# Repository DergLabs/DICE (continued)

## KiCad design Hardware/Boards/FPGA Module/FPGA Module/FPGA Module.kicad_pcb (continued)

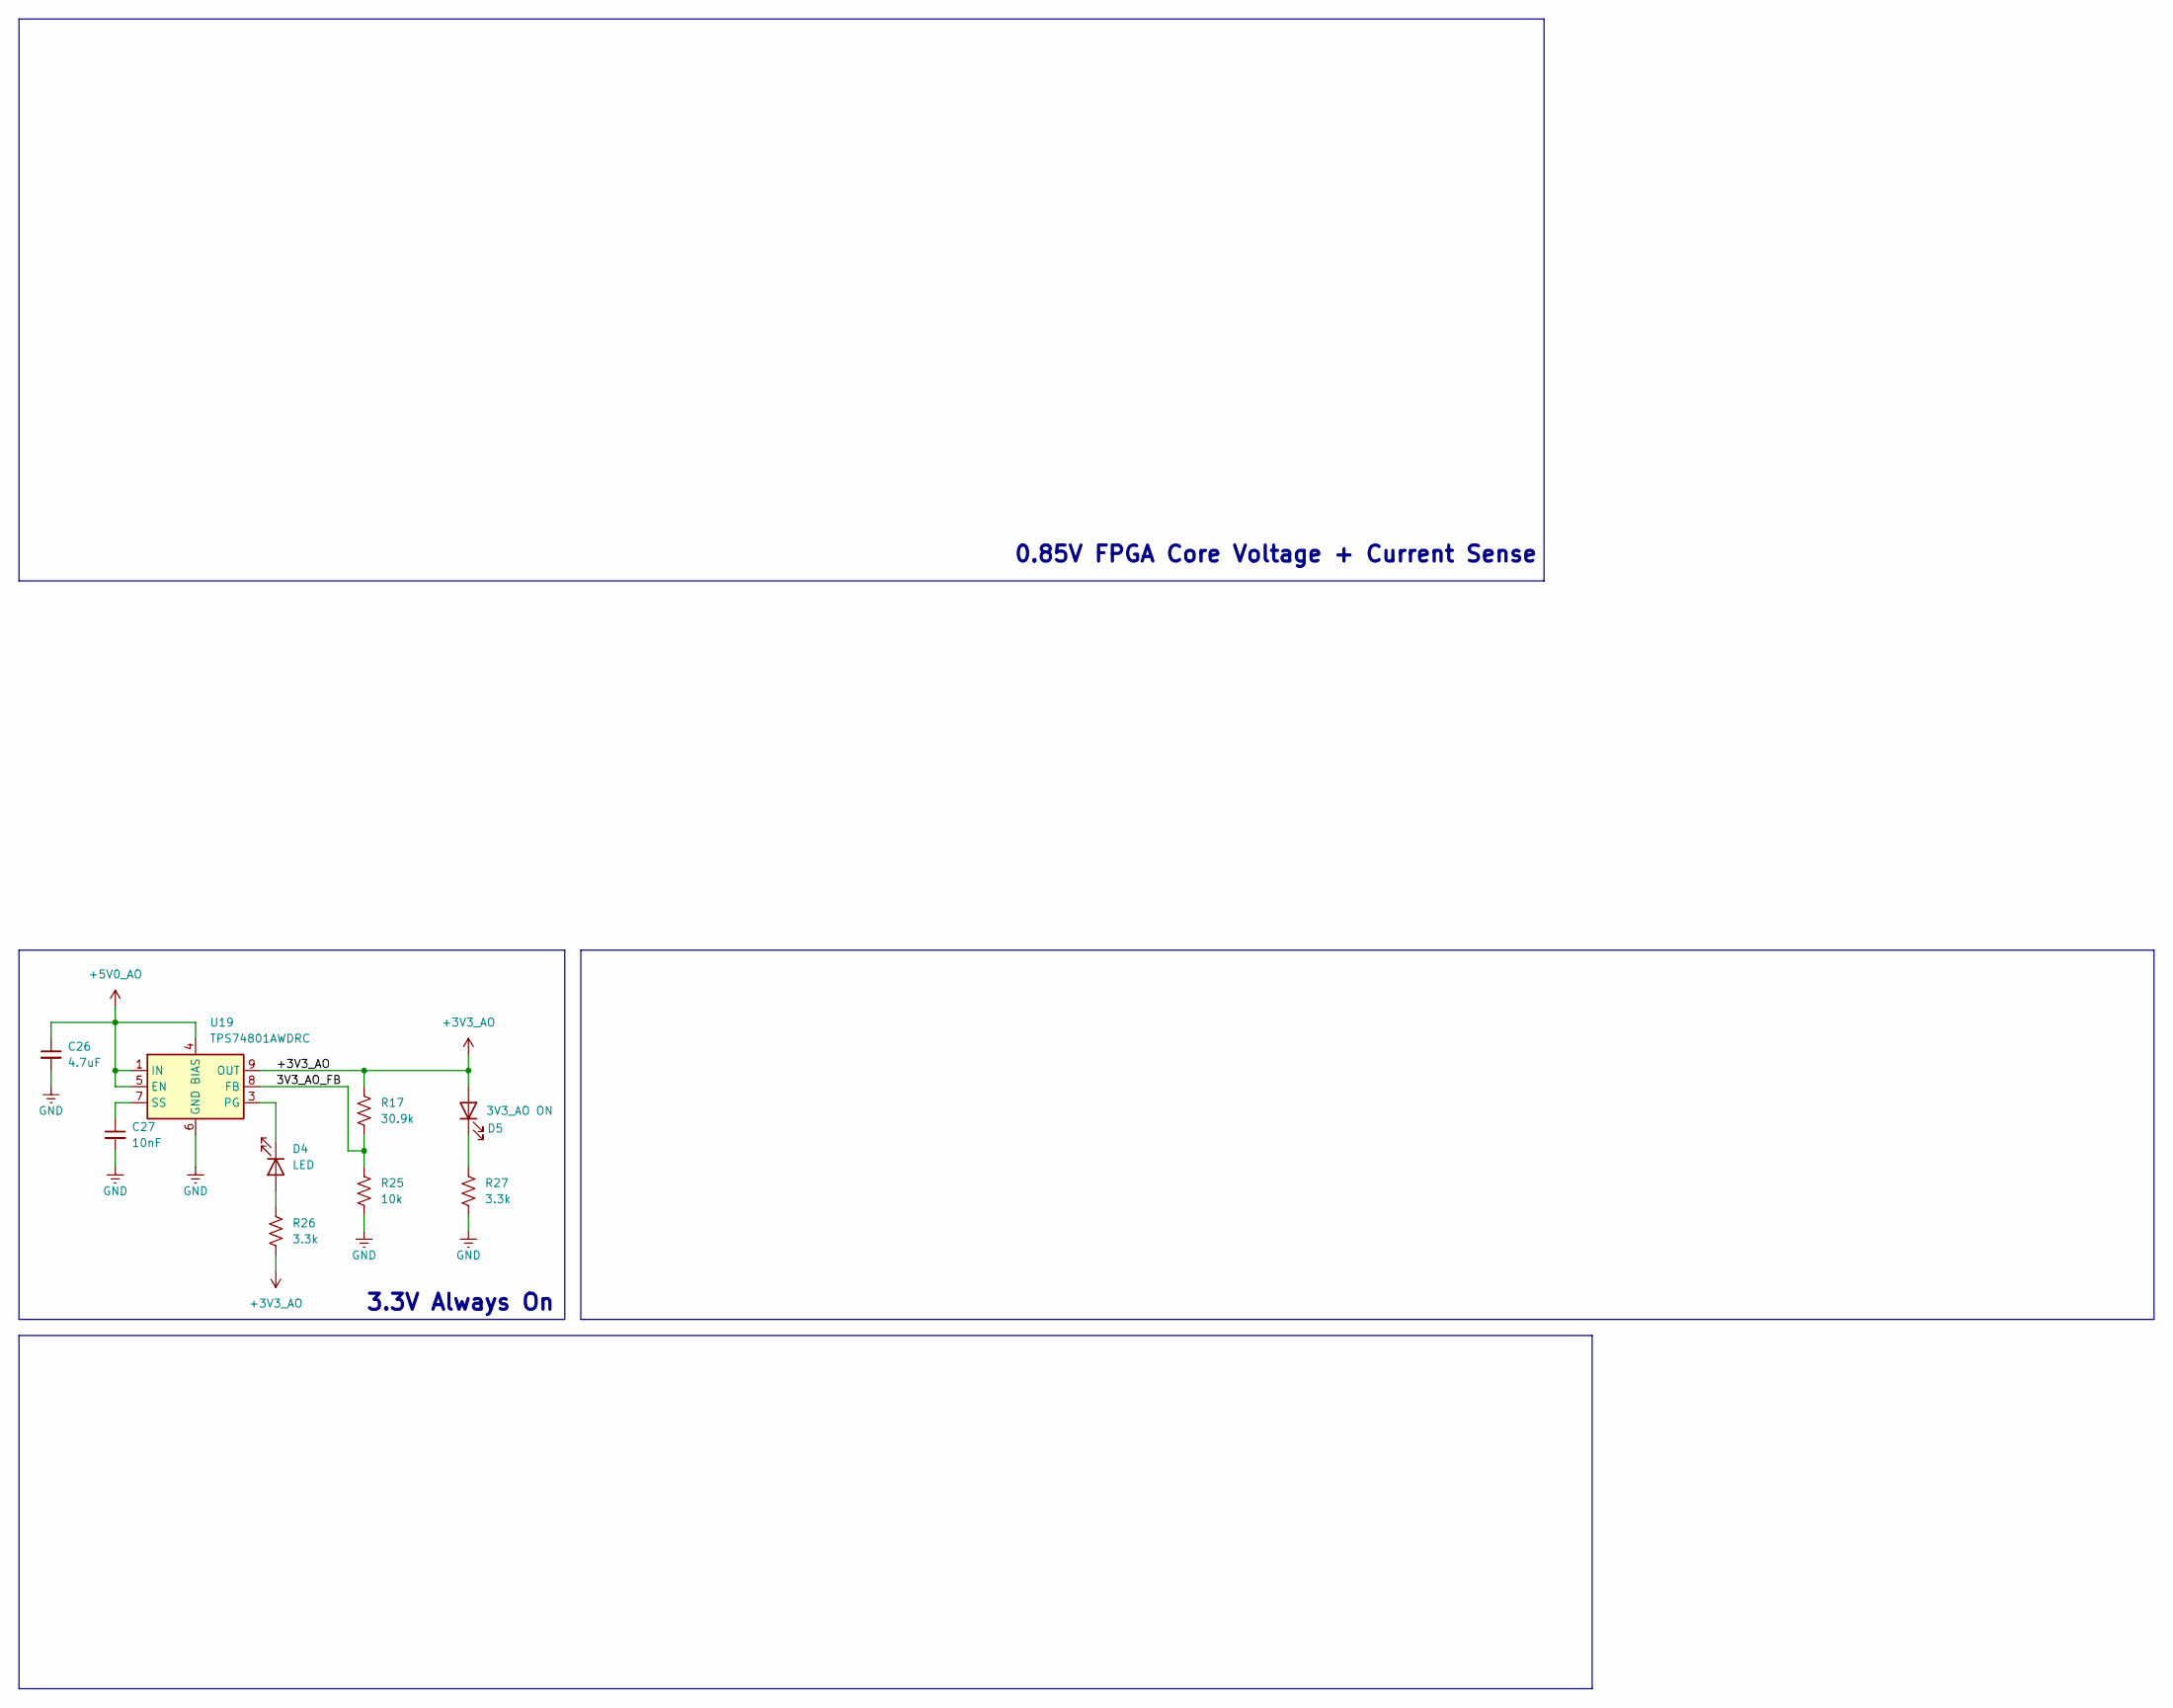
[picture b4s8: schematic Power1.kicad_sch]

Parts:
C26: 4.7uF; C_0402_1005Metric
C27: 10nF; C_0402_1005Metric
D4: LED; LED_0603_1608Metric
D5: 3V3_AO ON; LED_0603_1608Metric
R17: 30.9k; R_0402_1005Metric
R25: 10k; R_0402_1005Metric
R26, R27: 3.3k; R_0402_1005Metric
U19: TPS74801AWDRC; VSON-10-1EP_3x3mm_P0.5mm_EP1.65x2.4mm_ThermalVias

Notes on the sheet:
3.3V Always On
0.85V FPGA Core Voltage + Current Sense

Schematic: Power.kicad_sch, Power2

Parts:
C73, C85, C88, C89, C90: 1uF; C_0402_1005Metric
C77, C78, C79, C80, C81, C82, C83, C84, C146, C147, C148, C161, C162, C163: 22uF; C_0805_2012Metric
C86, C94, C102, C110, C118, C149, C164, C174, C175, C176, C177: 100nF; C_0201_0603Metric
C87, C92: 4.7uF; C_0402_1005Metric
C91, C186: 10uF; C_0603_1608Metric
C140, C141, C142, C143: 1nF; C_0201_0603Metric; not fitted
C144, C145, C166, C169, C170, C171, C172, C173: 47uF; C_0603_1608Metric
C150, C160, C165: 220nF; C_0201_0603Metric
C151: 2.2nF; C_0402_1005Metric
C152, C153, C154, C157: 100uF; C_0805_2012Metric
C155, C156: 560uF; CP_EIA-7343-31_Kemet-D; MPN EEF-GX0D561R
C158, C159, C167, C168: 4.7uF; C_0201_0603Metric
C178, C180, C182, C184: 4.7pF; C_0201_0603Metric
C179, C181, C183, C185: 220pF; C_0201_0603Metric
D7: 0V85 PG; LED_0603_1608Metric
D8: 3V3 PG; LED_0603_1608Metric
D9: 1V8 PG; LED_0603_1608Metric
D10: 1V2 PG; LED_0603_1608Metric
D11: 0V9 PG; LED_0603_1608Metric
L1, L4: 220nH; IND_SRP6530A_BRN; MPN PA5041.221HLT
L2, L5: 560nH; L_Bourns_SRP3012; MPN SRP3012TA-R56M
L3: 1uH; L_1210_3225Metric; MPN SRP3212A-1R0M
L7: 300nH; L_Taiyo-Yuden_MD-3030; MPN MDMK3030TR30MM
R56: 500uOhm; R_1206_3216Metric; MPN HCS1206FT1L00
R57, R61, R67, R70, R76, R82, R85, R91, R94, R98, R99, R100, R101, R102, R105: 4.7K; R_0201_0603Metric
R58, R62, R68, R73, R78, R83, R87, R92, R96, R106: 33R; R_0201_0603Metric
R63: 33K; R_0201_0603Metric
R64: 56.2K; R_0201_0603Metric
R65, R132, R138, R140, R142, R143, R144, R145, R151, R154, R155, R157: 10K; R_0201_0603Metric
R66: 26.1K; R_0201_0603Metric
R133: 20K; R_0201_0603Metric
R134: 47K; R_0201_0603Metric
R135, R136, R146, R149, R152, R153, R161: 0R; R_0201_0603Metric
R137, R156: 2.2R; R_0603_1608Metric
R139: 14K; R_0201_0603Metric
R141: 8.06K; R_0201_0603Metric
R147, R167: 24K; R_0201_0603Metric
R148, R168: 81K; R_0201_0603Metric
R150: 0R; R_0201_0603Metric; not fitted
TP28, TP33, TP36, TP39, TP42, TP43, TP44, TP45, TP46, TP47: Test Point; Test Point 0.75mm
U9: LT7200S
U10: L78L33_SOT89; SOT-89-3
U11: INA236; SOT-23-8
U13, U15, U17, U19: INA700AYWFR; INA700_AYWFR
U24, U25: MP8796; TQFN-4x5_MP8796B_MNP

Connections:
+0V9: TP33.1, U13.A1 (IN-); also elsewhere on the board
+0V85: R56.2, TP28.1, U11.2 (IN-); also elsewhere on the board
+1V2: TP36.1, U15.A1 (IN-); also elsewhere on the board
+1V8: TP39.1, U17.A1 (IN-); also elsewhere on the board
/Top/Board to Boards/PP_VUSB: C73.1, C77.1, C78.1, C79.1, C80.1, C81.1, C82.1, C83.1, C84.1, C85.1, C88.1, C89.1, C90.1, C146.1, C147.1, C148.1, C149.1, C161.1, C162.1, C163.1, C164.1, C186.1, U9.4 (PVIN2), U9.5 (PVIN2), U9.10 (SVIN), U9.11 (PVIN1), U9.28 (PVIN4), U9.29 (PVIN4), U9.34 (PVIN3), U9.35 (PVIN3), U10.3 (IN), U24.1 (VIN), U24.16 (VIN), U25.1 (VIN), U25.16 (VIN); also elsewhere on the board
/Top/Power/0V9_EN: R101.2, TP45.1, U9.20 (RUN4); also elsewhere on the board
/Top/Power/0V9_FB: C143.2, R141.1, R145.2, U9.22 (FB4)
/Top/Power/0V9_ISNS_ALERT: R70.1, U13.C2 (ALRT); also elsewhere on the board
/Top/Power/0V9_ISNS_I2C0_SCL: R68.1, U13.C3 (SCL)
/Top/Power/0V9_ISNS_I2C0_SDA: R73.1, U13.B3 (SDA)
/Top/Power/0V9_LX: L7.1, U9.30 (SW4), U9.31 (SW4)
/Top/Power/0V9_PG: D11.2 (A), R94.1, U9.24 (PGOOD4)
/Top/Power/0V85_EN: R102.2, TP46.1, U24.9 (EN), U25.9 (EN); also elsewhere on the board
/Top/Power/0V85_ISNS_ALERT: R61.1, U11.8 (ALERT); also elsewhere on the board
/Top/Power/0V85_ISNS_I2C0_SCL: R58.1, U11.5 (SCL)
/Top/Power/0V85_ISNS_I2C0_SDA: R62.1, U11.6 (SDA)
/Top/Power/0V85_PG: D7.2 (A), R57.1, U24.10 (PG), U25.10 (PG)
/Top/Power/0V85_SNS: C152.1, C153.1, C154.1, C155.1, C156.1, C157.1, L1.2, L4.2, R56.1, R135.1, U11.1 (IN+)
/Top/Power/0V85_SNS_N: R134.1, R136.2, U24.21 (RGND), U25.21 (RGND)
/Top/Power/0V85_SNS_P: C151.1, R133.2, R135.2
/Top/Power/1V2_EN: R100.2, TP44.1, U9.43 (RUN3); also elsewhere on the board
/Top/Power/1V2_FB: C142.2, R139.1, R140.2, U9.41 (FB3)
/Top/Power/1V2_ISNS_ALERT: R82.1, U15.C2 (ALRT); also elsewhere on the board
/Top/Power/1V2_ISNS_I2C0_SCL: R78.1, U15.C3 (SCL)
/Top/Power/1V2_ISNS_I2C0_SDA: R83.1, U15.B3 (SDA)
/Top/Power/1V2_LX: L2.1, U9.32 (SW3), U9.33 (SW3)
/Top/Power/1V2_PG: D10.2 (A), R85.1, U9.39 (PGOOD3)
/Top/Power/1V8_EN: R99.2, TP43.1, U9.44 (RUN2); also elsewhere on the board
/Top/Power/1V8_FB: C141.2, R66.1, R132.2, U9.46 (FB2)
/Top/Power/1V8_ISNS_ALERT: R91.1, U17.C2 (ALRT); also elsewhere on the board
/Top/Power/1V8_ISNS_I2C0_SCL: R87.1, U17.C3 (SCL)
/Top/Power/1V8_ISNS_I2C0_SDA: R92.1, U17.B2 (A0), U17.B3 (SDA)
/Top/Power/1V8_LX: L5.1, U9.6 (SW2), U9.7 (SW2)
/Top/Power/1V8_PG: D9.2 (A), R76.1, U9.48 (PGOOD2)
/Top/Power/3V3_AON: C91.1, R57.2, R67.2, R76.2, R85.2, R94.2, U10.1 (OUT); also elsewhere on the board
/Top/Power/3V3_EN: R98.2, TP42.1, U9.19 (RUN1); also elsewhere on the board
/Top/Power/3V3_FB: C140.2, R64.1, R65.2, U9.17 (FB1)
/Top/Power/3V3_ISNS_ALERT: R105.1, U19.C2 (ALRT); also elsewhere on the board
/Top/Power/3V3_ISNS_I2C0_SCL: R96.1, U19.B2 (A0), U19.C3 (SCL)
/Top/Power/3V3_ISNS_I2C0_SDA: R106.1, U19.B3 (SDA)
/Top/Power/3V3_LX: L3.1, U9.8 (SW1), U9.9 (SW1)
/Top/Power/3V3_PG: D8.2 (A), R67.1, U9.15 (PGOOD1)
/Top/Power/+0V9_SNS: C143.1, C172.1, C173.1, L7.2, R141.2, U13.A3 (IN+)
/Top/Power/+1V2_SNS: C142.1, C170.1, C171.1, L2.2, R139.2, U15.A3 (IN+)
/Top/Power/+1V8_SNS: C141.1, C166.1, C169.1, L5.2, R66.2, U17.A3 (IN+)
/Top/Power/+3V3_SNS: C118.1, C140.1, C144.1, C145.1, L3.2, R64.2, U19.A3 (IN+), U19.C1 (VS)
/Top/Power/I2C0_SCL: R58.2, R68.2, R78.2, R87.2, R96.2; also elsewhere on the board
/Top/Power/I2C0_SDA: R62.2, R73.2, R83.2, R92.2, R106.2; also elsewhere on the board
/Top/Power/INTVCC: C87.1, C92.1, R146.2, U9.25 (INTVCC)
/Top/Power/ISUM: R153.1, U25.19 (ISUM)
/Top/Power/PASS_1: R149.1, U25.12 (TAKE)
/Top/Power/SET: R152.1, U25.13 (SET)
/Top/Power/VCORE_LX1: C150.1, L1.1, U24.2 (SW), U24.3 (SW)
/Top/Power/VCORE_LX2: C165.1, L4.1, U25.2 (SW), U25.3 (SW)
/Top/Power/VCORE_VCC: C158.1, C167.1, R137.2, R138.2, R142.2, R143.2, R144.2, R156.2, U24.24 (VCC), U25.24 (VCC)
/Top/Power/VCORE_VFB: C151.2, R133.1, R134.2, U24.22 (FB), U25.22 (FB)
/Top/Power/VCORE_VRDV1: C159.1, R137.1, U24.5 (VDRV)
/Top/Power/VCORE_VRDV2: C168.1, R156.1, U25.5 (VDRV)
/Top/Power/VMODE: R144.1, U24.8 (MODE), U25.8 (MODE)
/Top/Power/VPMODE: R143.1, U24.7 (PMODE), U25.7 (PMODE)
/Top/Power/VRAMP: R142.1, U24.6 (RAMP), U25.6 (RAMP)
/Top/Power/VTAKE: R138.1, R161.1, U24.12 (TAKE)
unnamed: C179.1, R151.1
unnamed: C181.1, R154.1
unnamed: C183.1, R155.1
unnamed: C185.1, R157.1
unnamed: C178.1, R151.2, U9.18 (ITH1)
unnamed: C180.1, R154.2, U9.45 (ITH2)
unnamed: C182.1, R155.2, U9.42 (ITH3)
unnamed: C184.1, R157.2, U9.21 (ITH4)
unnamed: R146.1, R150.1, U9.14 (MODE/SYNC)
unnamed: R63.2, U9.38 (RT)
unnamed: C174.1, U9.16 (TRACK1)
unnamed: C175.1, U9.47 (TRACK2)
unnamed: C176.1, U9.40 (TRACK3)
unnamed: C177.1, U9.23 (TRACK4)
unnamed: C150.2, U24.25 (BST)
unnamed: R147.2, U24.17 (FREQ)
unnamed: R148.2, U24.20 (ILIM)
unnamed: R153.2, U24.19 (ISUM)
unnamed: R149.2, U24.11 (PASS)
unnamed: R152.2, U24.13 (SET)
unnamed: C160.1, U24.18 (SS)
unnamed: C165.2, U25.25 (BST)
unnamed: R167.2, U25.17 (FREQ)
unnamed: R168.2, U25.20 (ILIM)
unnamed: R161.2, U25.11 (PASS)

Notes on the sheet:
NOTE: Place large thermal GND plane below Place on TOP side for heatsinking
NOTE: I2C ADDR is 0x46
NOTE: Configured for 1Mhz, 6.6ms SS, 22A ILIM
NOTE: I2C ADDR is 0x45
NOTE: 2x22uF per PVIN Bank Place 1uF Caps on Vin pins
NOTE: Vout = 0.5(1-[R2/10K]) R2 = 10K([Vout/0.5] - 1)
NOTE: I2C ADDR is 0x44
NOTE: I2C ADDR is 0x48 Set Full scale range to 20mV
NOTE: I2C ADDR is 0x47
0.85V @ 40A
1V2 3A
1V8 3A
0V9 3A
3V3 3A

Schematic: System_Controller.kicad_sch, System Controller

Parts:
C64, C72: 1uF; C_0201_0603Metric
C65, C66, C67, C68, C69, C70, C71, C74: 100nF; C_0201_0603Metric
C75, C76: 18pF; C_0201_0603Metric
D6: MCU Heartbeat; LED_0603_1608Metric
R50: 10K; R_0201_0603Metric; MPN RC0402JR-0710KL
R51: 3.3K; R_0201_0603Metric
R52, R53, R54, R55: 1K; R_0201_0603Metric
SW1: RST; SW_Push_SPST_NO_Alps_SKRK
TP21, TP24, TP25, TP26, TP27: Test Point; Test Point 0.75mm
TP22, TP23: TestPoint; Test Point 0.75mm
U7: W25Q16JVUXIQ TR; USON-8_UX_2x3x0p6_WIN
U8: RP2040; QFN-56-1EP_7x7mm_P0.4mm_EP3.2x3.2mm
Y1: 12Mhz; Oscillator_SMD_Abracon_ASE-4Pin_3.2x2.5mm

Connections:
/Top/Board to Boards/USB_SYSMON_D_N: U8.46 (USB_DM); also elsewhere on the board
/Top/Board to Boards/USB_SYSMON_D_P: U8.47 (USB_DP); also elsewhere on the board
/Top/Clock Generator/I2C1_SCL: R52.1, TP27.1, U8.9 (GPIO7); also elsewhere on the board
/Top/Clock Generator/I2C1_SDA: R53.1, TP26.1, U8.8 (GPIO6); also elsewhere on the board
/Top/Clock Generator/MCU_CLK: U8.2 (GPIO0); also elsewhere on the board
/Top/DDR4/2V5_EN: U8.32 (GPIO21); also elsewhere on the board
/Top/LVL_SHIFT_EN: U8.35 (GPIO23); also elsewhere on the board
/Top/Power/0V9_EN: U8.17 (GPIO14); also elsewhere on the board
/Top/Power/0V9_ISNS_ALERT: U8.12 (GPIO9); also elsewhere on the board
/Top/Power/0V85_EN: U8.16 (GPIO13); also elsewhere on the board
/Top/Power/0V85_ISNS_ALERT: U8.11 (GPIO8); also elsewhere on the board
/Top/Power/1V2_EN: U8.18 (GPIO15); also elsewhere on the board
/Top/Power/1V2_ISNS_ALERT: U8.13 (GPIO10); also elsewhere on the board
/Top/Power/1V8_EN: U8.31 (GPIO20); also elsewhere on the board
/Top/Power/1V8_ISNS_ALERT: U8.14 (GPIO11); also elsewhere on the board
/Top/Power/3V3_AON: C67.1, C68.1, C69.1, C70.1, C71.1, C72.1, C74.1, R52.2, R53.2, R54.2, R55.2, U7.8 (VCC), U8.1 (IOVDD), U8.10 (IOVDD), U8.22 (IOVDD), U8.33 (IOVDD), U8.42 (IOVDD), U8.43 (ADC_AVDD), U8.44 (VREG_IN), U8.48 (USB_VDD), U8.49 (IOVDD); also elsewhere on the board
/Top/Power/3V3_EN: U8.34 (GPIO22); also elsewhere on the board
/Top/Power/3V3_ISNS_ALERT: U8.15 (GPIO12); also elsewhere on the board
/Top/Power/I2C0_SCL: R54.1, TP25.1, U8.7 (GPIO5); also elsewhere on the board
/Top/Power/I2C0_SDA: R55.1, TP24.1, U8.6 (GPIO4); also elsewhere on the board
/Top/SYS_SPI_CS: U8.28 (GPIO17); also elsewhere on the board
/Top/SYS_SPI_MISO: U8.27 (GPIO16); also elsewhere on the board
/Top/SYS_SPI_MOSI: U8.30 (GPIO19); also elsewhere on the board
/Top/SYS_SPI_SCK: U8.29 (GPIO18); also elsewhere on the board
/Top/System Controller/MCU_HB_LED: R51.1, U8.37 (GPIO25)
/Top/System Controller/MCU_XI: C75.1, U8.20 (XIN), Y1.1
/Top/System Controller/MCU_XO: C76.1, U8.21 (XOUT), Y1.3
/Top/System Controller/QSPI_CLK: U7.6 (CLK), U8.52 (QSPI_SCLK)
/Top/System Controller/QSPI_CS: R50.1, U7.1 (/CS), U8.56 (QSPI_SS)
/Top/System Controller/QSPI_D0: U7.5 (DI(IO0)), U8.53 (QSPI_SD0)
/Top/System Controller/QSPI_D1: U7.2 (DO(IO1)), U8.55 (QSPI_SD1)
/Top/System Controller/QSPI_D2: U7.3 (/WP(IO2)), U8.54 (QSPI_SD2)
/Top/System Controller/QSPI_D3: U7.7 (/HLD/RST(IO3)), U8.51 (QSPI_SD3)
/Top/System Controller/VMCU_1V1: C64.1, C65.1, C66.1, TP21.1, U8.23 (DVDD), U8.45 (VREG_VOUT), U8.50 (DVDD)
unnamed: D6.2 (A), R51.2
unnamed: R50.2, SW1.2 (B)
unnamed: TP22.1, U8.24 (SWCLK)
unnamed: TP23.1, U8.25 (SWD)

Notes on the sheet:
NOTE: 3V3 DCDC Must be enabled before using i2c
System Controller MCU

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
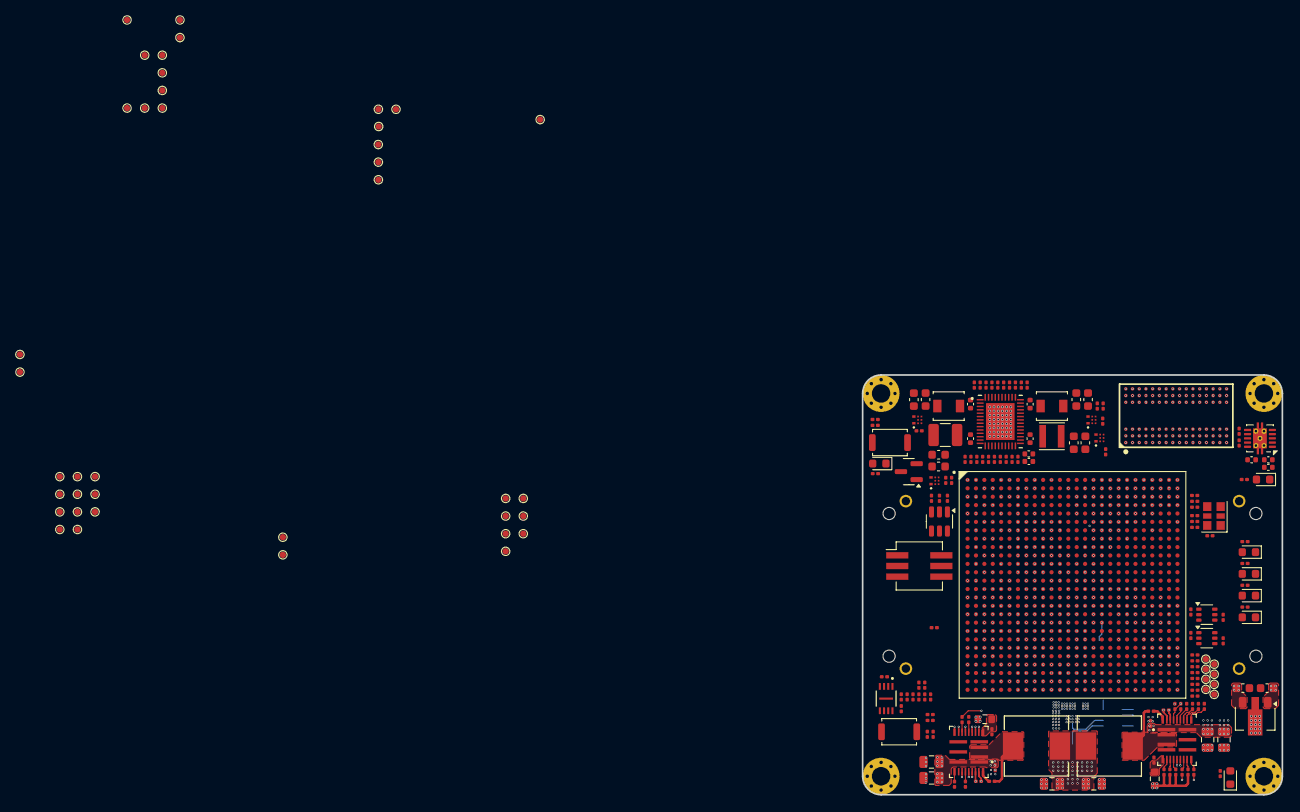
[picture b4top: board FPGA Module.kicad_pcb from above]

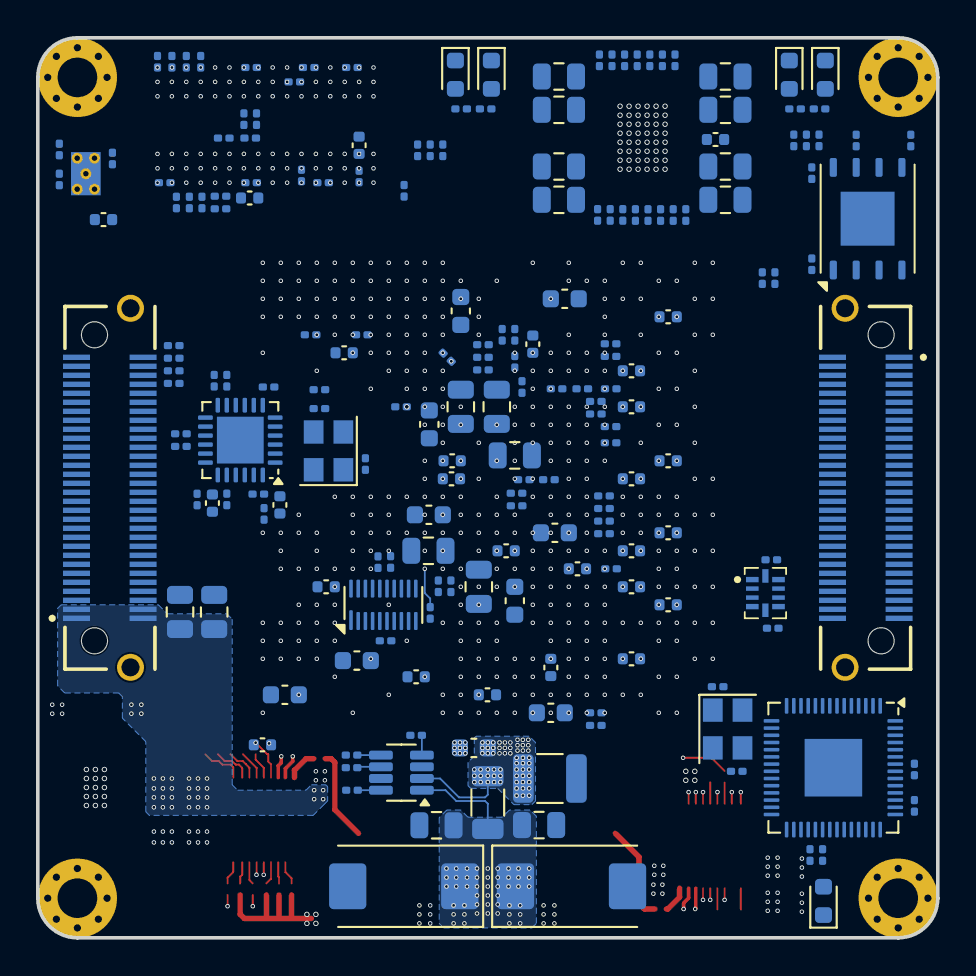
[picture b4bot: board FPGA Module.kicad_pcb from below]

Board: 8 copper layers, 50.0 x 50.0 mm, 405 parts (195 on the bottom side), 349 nets.

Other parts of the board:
R1, R2: 33R; R_0201_0603Metric
TP1, TP2, TP3, TP4: Mounting Hole; MountingHole_2.2mm_M2_Pad_Via

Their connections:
/Top/Board to Boards/FPGA_I2C_SCL: R1.2; also elsewhere on the board
/Top/Board to Boards/FPGA_I2C_SDA: R2.2; also elsewhere on the board
/Top/Clock Generator/I2C1_SCL: R1.1; also elsewhere on the board
/Top/Clock Generator/I2C1_SDA: R2.1; also elsewhere on the board

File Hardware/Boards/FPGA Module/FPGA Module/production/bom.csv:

Designator,Footprint,Quantity,Value,LCSC Part #
"C1, C102, C110, C118, C119, C120, C121, C122, C123, C124, C125, C127, C128, C129, C130, C131, C132, C149, C164, C174, C175, C176, C177, C2, C3, C4, C49, C5, C50, C51, C52, C57, C58, C59, C6, C60, C65, C66, C67, C68, C69, C7, C70, C71, C74, C86, C94",0201,47,100nF,
"C10, C21, C22, C27, C28, C30, C33, C41, C43, C9",0402,10,10uF,
"C11, C144, C145, C166, C169, C170, C171, C172, C173, C20, C23, C26, C29, C31, C32, C40, C42, C8",0603,18,47uF,
"C12, C126, C13, C133, C14, C15, C158, C159, C16, C167, C168, C17, C18, C19, C24, C25, C44, C45, C46, C48, C55, C63, C87, C92",0201,24,4.7uF,
"C134, C135, C47, C56, C93, C95",0201,6,10nF,
"C137, C138, C75, C76",0201,4,18pF,
"C140, C141, C142, C143",0201,4,1nF,
"C146, C147, C148, C161, C162, C163, C77, C78, C79, C80, C81, C82, C83, C84",0805,14,22uF,
"C150, C160, C165",0201,3,220nF,
C151,0201,1,1.8nF,
"C152, C153, C154, C157, C34, C35, C36, C37, C38",0805,9,100uF,
"C155, C156",CP_EIA-7343-31_Kemet-D,2,560uF,EEF-GX0D561R
"C178, C180, C182, C184",0201,4,4.7pF,
"C179, C181, C183, C185",0201,4,220pF,
"C186, C91",0603,2,1uF,
C39,1210,1,330uF,
"C53, C54, C61, C62",0201,4,470nF,
"C64, C72",0201,2,1uF,
"C73, C85, C88, C89, C90",0402,5,1uF,
D1,0603,1,LED3,
D10,0603,1,1V2 PG,
D11,0603,1,0V9 PG,
D12,0603,1,DONE,
D2,0603,1,LED2,
D3,0603,1,LED1,
D4,0603,1,LED0,
D5,0603,1,2V5 ON,
D6,0603,1,MCU Heartbeat,
D7,0603,1,0V85 PG,
D8,0603,1,3V3 PG,
D9,0603,1,1V8 PG,
"FB1, FB2, FB3, FB4",0201,4,BKP0603HS121,
"J1, J2",SAMTEC_LSHM-130-XX.X-XXX-DV-A-S-K-XX,2,LSHM-130-XX.X-XXX-DV-A-S-K-XX,
"L1, L4",IND_SRP6530A_BRN,2,220nH,PA5041.221HLT
"L2, L5",L_Bourns_SRP3012,2,560nH,SRP3012TA-R56M
L3,1210,1,1uH,SRP3212A-1R0M
L7,L_Taiyo-Yuden_MD-3030,1,300nH,MDMK3030TR30MM
Q10,SOT-23,1,IRLML6244,
"Q6, Q7",SOT-363_SC-70-6,2,FDG1024NZ,
"R1, R106, R108, R109, R110, R111, R129, R130, R131, R2, R41, R43, R58, R62, R68, R73, R78, R83, R87, R92, R96",0201,21,33R,
"R10, R11, R12, R14, R15, R32, R33, R34, R35, R52, R53, R54, R55, R6, R7, R9",0201,16,1K,
"R100, R101, R102, R105, R112, R113, R118, R119, R120, R121, R122, R124, R125, R127, R128, R40, R45, R48, R57, R61, R67, R70, R76, R82, R85, R91, R94, R98, R99",0201,29,4.7K,
R114,0201,1,2.4K,
"R123, R126, R135, R136, R146, R149, R150, R152, R153, R161, R4, R71, R72, R74",0201,14,0R,
"R13, R24, R25, R26, R27, R28, R29, R30, R31, R44, R46, R5, R8",0201,13,100R,
"R132, R138, R140, R142, R143, R144, R145, R151, R154, R155, R157, R16, R17, R18, R19, R20, R21, R22, R23, R37, R65",0201,21,10K,
R133,0201,1,20K,
R134,0201,1,47K,
"R137, R156",0603,2,2.2R,
R139,0201,1,14K,
R141,0201,1,8.06K,
"R147, R167",0201,2,24K,
"R148, R168",0201,2,81K,
"R3, R42",0201,2,240R,
R36,0201,1,100K,
"R38, R51",0201,2,3.3k,
R39,0201,1,5.1K,
"R47, R49",0201,2,499R,
R50,0201,1,10K,RC0402JR-0710KL
R56,1206,1,500uOhm,HCS1206FT1L00
R63,0201,1,33K,
R64,0201,1,56.2K,
R66,0201,1,26.1K,
"SW1, SW2",SW_Push_SPST_NO_Alps_SKRK,2,RST,
"TP1, TP2, TP3, TP4",MountingHole_2.2mm_M2_Pad_Via,4,Mounting Hole,
"TP10, TP19, TP20, TP21, TP24, TP25, TP26, TP27, TP28, TP29, TP30, TP31, TP32, TP33, TP36, TP39, TP42, TP43, TP44, TP45, TP46, TP47, TP5, TP50, TP51, TP52, TP53, TP54, TP55, TP56, TP57, TP6, TP7, TP8, TP9",Test Point 0.5mm No Silk,35,Test Point,
TP11,Test Point 0.5mm No Silk,1,IO0,
TP12,Test Point 0.5mm No Silk,1,IO4,
TP13,Test Point 0.5mm No Silk,1,IO1,
TP14,Test Point 0.5mm No Silk,1,IO5,
TP15,Test Point 0.5mm No Silk,1,IO2,
TP16,Test Point 0.5mm No Silk,1,IO6,
TP17,Test Point 0.5mm No Silk,1,IO3,
TP18,Test Point 0.5mm No Silk,1,IO7,
"TP22, TP23",Test Point 0.5mm No Silk,2,TestPoint,
U1,BGA676,1,XCKU3P-FFVA676,
U10,SOT-89-3,1,L78L33_SOT89,
U11,SOT-23-8,1,INA236,
"U13, U15, U17, U19",INA700_AYWFR,4,INA700AYWFR,
U2,USON-20_2x4mm_P0.4mm,1,TXB0108DQSR,
U20,W-PDFN-8-1EP_6x5mm_P1.27mm_EP3x3mm,1,MT25QUxxxxxx1xW7,
U21,SOT-23-6,1,MAX6070BAUT12V+T,
U22,TS3USB,1,TS3USB221A,
U23,QFN-24-1EP_4x4mm_P0.5mm_EP2.6x2.6mm,1,Si5338A-B-GMR,
"U24, U25",TQFN-4x5_MP8796B_MNP,2,MP8796,
U3,Oscillator_SMD_SiTime_SiT9121-6Pin_3.2x2.5mm,1,Si511J200,
U4,VSON-10-1EP_3x3mm_P0.5mm_EP1.65x2.4mm_ThermalVias,1,TPS74801AWDRC,
U5,BGA96C80P9X16_750X1350X120,1,MT40A512M16LY-075:E,
U7,USON-8_UX_2x3x0p6_WIN,1,W25Q16JVUXIQ TR,
U8,QFN-56-1EP_7x7mm_P0.4mm_EP3.2x3.2mm,1,RP2040,
U9,LT7200S,1,LT7200S,
"Y1, Y2",Oscillator_SMD_Abracon_ASE-4Pin_3.2x2.5mm,2,12Mhz,

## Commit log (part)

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2024-04-08 Added ToE slides
    Added ToE powerpoint and PDF slides
2024-04-08 Updated slides
    Added sections to slides
2024-07-13 Added Board Directories
2024-07-13 Created project files for FPGA module
2024-07-15 Updated IO Module Schematics
    Added Power, USB hub and USB-JTAG circuits
2024-07-15 Updated IO Module Schematics
    Added MCU, JTAG and FIFO circuits
2024-07-16 Completed IO Module Schematics
2024-07-17 Updated SCH with notes & annotations
2024-07-20 Updated PCB routing for IO Module
2024-07-20 Completed IO Module PCB Layout
2024-07-20 syncing files
2024-07-20 add 3D model for FPGA
2024-07-21 Added FPGA Footprint & Symbol
2024-07-21 FPGA module schematic page creation
2024-07-21 Added 6mm B2B 3d model to IO module
2024-07-22 Cleaned up routing for IO module
2024-07-24 FPGA Module schematic and part edits
2024-07-24 Updated Library Structure
2024-07-24 Fixed library structure
2024-07-24 FPGA Board schematic work
2024-07-24 Added pin voltages to IO module b2b
2024-07-25 FPGA Module Schematic work
2024-07-25 Added DDR sch in FPGA module
2024-07-25 FPGA Module Power Schematic Changes
2024-07-25 Added FPGA Config page
2024-07-29 Added reference designs to Boards folder, updated FPGA IO to include DDR pins
2024-07-29 Added new datasheets and reference images
2024-07-31 minor FPGA schematic changes
2024-08-01 updated fpga module schematics
2024-08-04 Update FPGA Module Netclasses
2024-08-04 Added Top sheet connections for FPGA module
2024-08-05 Added NC to unused pins
2024-08-07 Cleaned up IO Module and went through DRC errors
2024-08-14 FPGA Module sch update
    Added 3V3 LDO for MCU and 3V3 EN for DCDC. Also added SPI bus from MCU to FPGA with level shifter
2024-08-24 Updated SCH and Layout
    Added temp sensors for DCDC's, Added MCU control for FPGA mode, removed mode DIP switch
2024-08-26 FPGA Layout update
    Added power panes & moved IO Buffer to MCU
2024-09-06 FPGA Module Routing Updates
    Modified DDR4 routing and FPGA IO Bus routing
2024-09-06 Updated FPGA Module Routing
    Cleaned up routing
2024-09-08 Updated DDR4 routing
2024-09-10 Completed FPGA Module Layout
2024-09-16 Fixed FPGA Module Routing
    Reversed B2B headers and re-routed connections to FPGA
2024-09-16 cleaned up fpga module
2024-09-16 Fixed trace on FPGA module
2024-09-17 Generated FPGA module gerbers
2024-09-18 Fixed Trace spacing (thx JLC)
2024-09-22 Ignore and remove MacOS .DS_* files
2024-09-22 Added skeleton firmware for io board
2024-09-24 Added PCB 3d models
2024-09-29 Fixed Clock, set pull-up restistor on USBPD_FLT_IN
2024-09-29 ignore .cache/ directory and compile_commands.json fiel
2024-09-29 Added Dedicated voltage reading
2024-09-29 Swap Endianness of reading from registers
2024-09-29 HDMI_R/W variable unused, deemed not necessary
2024-09-30 Created SPI Module FPGA Project
2024-10-01 created documentation folder for fpga
2024-10-01 Potential IO Board Fixes
2024-10-01 fixed byte order of ina700_read_32_reg()
2024-10-01 Edited SPI Module Project Organization
2024-10-01 Fixed IO Module firmware
    Voltage, current and power readings now work. temp readings still not correct
2024-10-01 Formatting, added I2C_SPEED constant
2024-10-01 Ignore .cache folder and KiCad ~ files
2024-10-01 Added FPGA Firmware Pin Initialization, need to add printing of values
2024-10-02 Fixed IO module firmware to read temperature correctly, added reset command to mcu
2024-10-02 removed commit message from code
2024-10-06 finished most of fpga firmware, Clock generator still in progress
2024-10-06 attempt at cleanup
2024-10-06 idek how this happened
2024-10-14 Reports when i2c devices are not found
2024-10-14 misc changes
2024-10-14 Updates to FPGA and IO Module, layout studies and reference designs
2024-10-19 Rev 2 IO module complete
2024-10-20 FPGA Module Rev 2 Layout Begun
2024-10-22 Completed B2B and HyperRam routing
2024-10-22 Minor routing updates
    cleaned up some traces
2024-10-27 Fixed false INA700 Error messages
2024-10-27 capitilazied variables previously named INA236_CONFIG_BUF and INA236_SHUNT_CAL_BUF
2024-10-27 Added gitignore
2024-10-29 Recreated FPGA Module Fab files with tented Vias
2024-10-29 fixed filepath
2024-10-29 Created HDMI Testbench for Sii1136
2024-10-30 Implemented Video mux for HDMI Controller
2024-11-02 create new xdc file for FT600
2024-11-04 FT600 Loopback Implemented and ready for hardware testing
2024-11-05 Will not not need to set clock on new board
2024-11-05 formatting and commented out command handling, moved readinds to inside loop
2024-11-05 Broke out functions and constants into header files
2024-11-05 Put all initalization code for each item together
2024-11-07 New pinouts for Rev2 IO Board
2024-11-08 Updated Schematics & created pixel combiner HDL
2024-11-10 Added Presentation Slides
2024-11-11 Minor FPGA Bom updates
2024-11-11 Added __pycache__ to ignore file for future use
2024-11-11 FPGA Rev2 Firmware: Redid pinouts
    Reassigned pins to new Rev 2 Pinouts
    Changed SPI speed from 40 to 50MHz
    Changed I2C speed from 400 to 100KHz
    Removed References to _0V9
2024-11-11 Ignore kicad temp files
2024-11-13 Set up power supplies and set FPGA to JTAG mode
2024-11-19 Modified I2C Speed and config ADC range mask
2024-11-20 Fixed HDMI Testbench issues, HDMI now working correctly
2024-11-25 Removed Backups folders
2024-11-25 Added PCB Dice logo
2024-11-26 Update FT600 Loopback Project
2024-12-01 Sample N temperature N times a second
    Made the 1 second blinking execute in a different core.
    Main core now samples multiple times a second to
    determine whether or not to turn off power supplies.
2024-12-03 Added Config step for IMX477 camera
    Minimum config should be set up for max resolutions.
    There's more settings that can be gathered that will be
    in future commits.
2024-12-03 Camera Boot Sequence and CLK changes
    FPGA CLK: 250MHz -> 150MHz
    IO CLK: 250MHz -> 200MHz
    IO Board: MCU sets up Camera and sets MBUS[0] high
2024-12-03 Created VHDL constants file
2024-12-03 Allow MCU to operate at higher clock speed, actually blink led in second core
2024-12-04 Fixed IMX477 read/write code
2024-12-08 Created module debugger board & modified camera test code
    Added IDELAY3, MIPI_DPHY_DCI IO buffer, DCI_RESET primitive, re-configured clocking for ISERDES3 to use single clock & built in inverter on CLKB
2024-12-11 modified FPGA MIPI code to add ready output, modified IO module FW to initialize camera after fpga rdy goes high
2024-12-12 modified io firmware and camera code
2024-12-12 Lots of FT600 Dev Changes
2024-12-15 hdl and stuff
    i dont even know I've been staring at vivado synthesis for 20 hours
2024-12-15 more hdl
2024-12-16 IMX219 Firmware
    - Added option in cmake to build for either IMX219 or IMX477
    - Added preprocessor guard to use either IMX477 or IMX219 header
2024-12-16 Fixed README
2024-12-18 FT600 FPGA Recieve with ILA added
2024-12-29 rc tool gives back image split up into blocks with stats
    - splits into a grid of NxN rectangles
    - determines avg of stddev of gradients
    - determines avg of stddev of laplacians
    - adds that text to the tile
    - recombines into a grid of tiles with stats
2024-12-29 Color specific tiles to have red hue based on laplacian and grad
2024-12-30 Added trackbars to dynamically modify thresholds and update
2024-12-30 Added readme for Reference Compression (rc)
2025-01-05 Adds different hue based on contribution of params
2025-01-06 Replace mean of std dev of rgb laplacian with variance of black and white laplacian
2025-01-10 FT600 Module improvents and HyperRam Proj
2025-01-12 Created laplacian calculation core
    Added RGB to Grascale core, laplacian kernel calculation core and mean+variance calculation core
2025-01-14 HyperRam Register Read Project
2025-01-18 LZSS Encoder Project Creation
2025-01-21 Completed Image Statistics module and created image compressor project
2025-01-23 LZSS Encoder Working Simulation
2025-01-23 Refined compressor core
    Fixed timing issues, added quantizer
2025-01-24 Fixed image stats core
2025-01-29 Reworked Reference Compression
2025-01-31 Created HW Accelerator Test bench
2025-02-01 improved transpose module to use FSM
2025-02-02 ft600 v1.5 and initial v2 modules
2025-02-06 fixed tilewise compression test python script
    help
2025-02-07 Modified compression core for larger tile sizes
2025-02-10 Added RGB to YCRCB module to core
2025-02-10 Added statistics to fpga encoder script
2025-02-11 Added image statistics to core
2025-02-11 Refactored test code to be more readable
2025-02-12 Added PyQT version of gui, testing if blocks can be sent
2025-02-12 Updated requirements for pyqt reference compression
2025-02-12 Script and core updates
2025-02-14 Added new huffman and LZSS encoding
2025-02-15 attempt at sending whole image
2025-02-17 Modified USB code to work properly on windows, replace lossy portions with lossless blocks
2025-02-17 More diagnostics
2025-02-17 Shay: Removed lines causing errors
2025-02-17 Added optimized SW DCT
2025-02-17 Removed images
2025-02-17 Update FPGA core channel quantization & sizing
    Increased Quantization amount for Cr and Cb channels, modified channel widths to make Cr and Cb 10 bits, and Y 12 bits, allows full utilization of 32bit packets
2025-02-17 removed reference images to reduce size
2025-02-17 Modified fpga encoder script to improve performance
2025-02-18 Updated & tested scripts on new FPGA architecture
2025-02-21 Attempt for transfer using Johns new code
2025-02-21 Statistics
2025-02-21 Attempt to view differences in processed and raw image
2025-02-23 Stats should be correct
2025-02-23 Calculation for compression ratio was wrong
2025-02-23 attempt at new lines and reducing width of compressed size
2025-02-23 cleanup
2025-02-27 code updates and cleanup
2025-02-27 Cleaned Up FPGA Code
2025-02-27 Cleaned up code comments
2025-02-28 Revert "Attempt to view differences in processed and raw image"
    This reverts commit 6ef3409ed94d6ca2c7e8911c88137f85046b0210.
2025-02-28 Better block repacement?
2025-02-28 corrected coords
2025-02-28 fixed diff check
2025-02-28 CrCb subsampling, and attempt at multiline label
2025-02-28 Added counts of blocks
2025-03-03 don't no longer compressing block by block
2025-03-03 Be able to select image
2025-03-05 Added zoom and pan to image views
2025-03-07 Small QOL improvements
2025-03-07 added constriction library
2025-03-10 Initial commit of hyperram controller, still needs some cleaning
2025-03-10 Added proper comments to files
2025-03-14 Cleaned up code, added some more metrics
2025-04-07 Testing image process python scripts
2025-04-08 Added diagrams, papers and presentations
2025-04-08 added diagrams
2025-04-22 Add clear naming convention for generics
2025-04-23 Current state of hyperram controller
2025-04-23 Added reset for FIFOs
2025-04-28 Rewrite to use valids instead of counters
    - change some IP's to behavioral
    - add valid signals
    - remove unnecessary shift regs
    - remove counters and unnecessary sync logic
2025-05-08 ODDR Test Project Creation
2025-05-08 Working ODDR Sim
2025-05-09 ODDR Test bitrstream generated
2025-05-16 added clock and no buf oddr to oddr test outputs
2025-05-20 Skeleton bits for saving and opening DICE file
2025-05-29 Synced old reference compression tool to this branch
    Added reference compression tool to begin modifying for compatibility with new processor core architecture
2025-05-30 Updated software to function correctly with new FPGA core
    - Modified to accept raw data from hold memory
    - Correctly extracts Tile ID
    - Embeds thresholds into image byte array
2025-05-30 Minor Software updates
2025-05-30 Major FPGA core overhaul
    Updated architecture to add input hold ram
    Updated statistics block
    Added selection logic
    Added test ZigZag encoder (not used atm)
    Optimized to operate at 500MHz (Confirmed working in hardware)
2025-05-30 update hw architecture diagram
2025-05-30 modified diagrams
2025-06-02 Moved diagrams outside of HW folder
2025-06-02 Added arithmetic encoder diagram
2025-06-02 Added reports and presentation
2025-06-05 Added diagram
2025-06-05 Added HyperRam controller from Oscar branch
2025-06-09 Removed test images
2025-06-09 Added hardware arithmetic encoder
2025-06-09 Added software model for arithmetic codec
2025-06-09 Removed test code
2025-06-09 Fixed hardware Zigzag encoder and software
